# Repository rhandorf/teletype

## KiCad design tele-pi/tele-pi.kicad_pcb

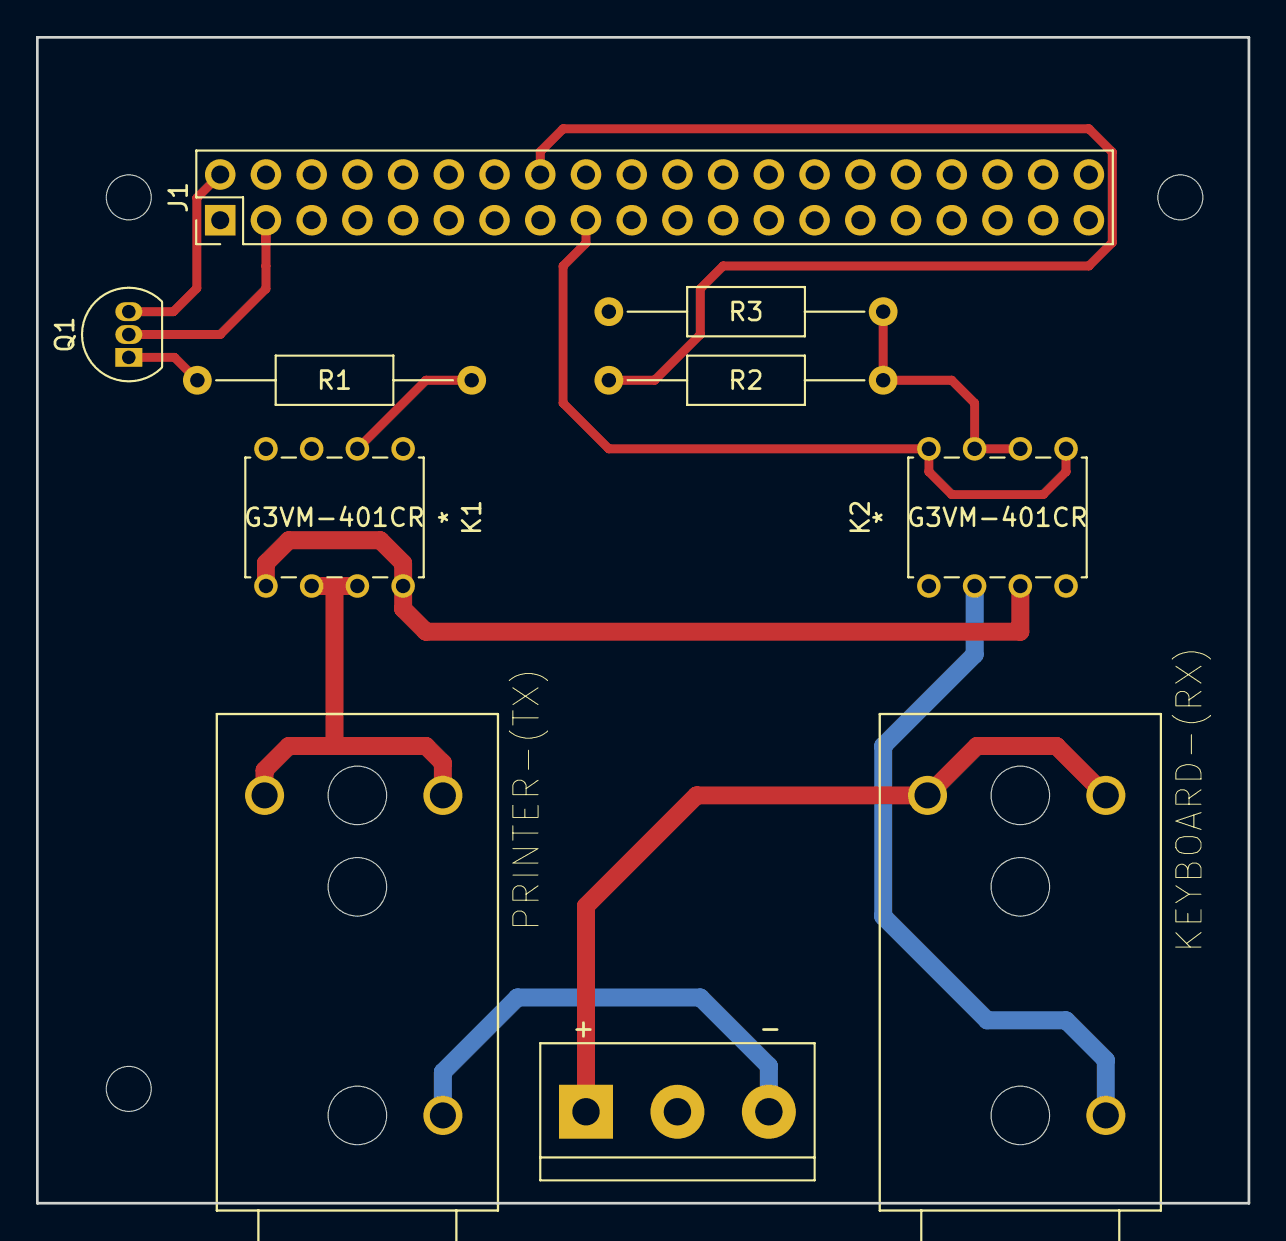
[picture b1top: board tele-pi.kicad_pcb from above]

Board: 2 copper layers, 67.3 x 64.8 mm, 10 parts (0 on the bottom side), 13 nets.

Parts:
+            -: 120VDC; TerminalBlock_bornier-3_P5.08mm
J1: Raspberry_Pi_2_3; PinHeader_2x20_P2.54mm_Vertical
K1, K2: G3VM-401CR
KEYBOARD-(RX): SN37A12A; SWITCHCRAFT_SN37A12A
PRINTER-(TX): SN37A12A; SWITCHCRAFT_SN37A12A
Q1: 2N3904; TO-92_Inline
R1, R2: 3.3k; R_Axial_DIN0207_L6.3mm_D2.5mm_P15.24mm_Horizontal
R3: 100; R_Axial_DIN0207_L6.3mm_D2.5mm_P15.24mm_Horizontal

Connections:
GND: J1.6, J1.9, J1.14, J1.20, J1.25, J1.30, J1.34, J1.39, K1.3, R3.1
unnamed: J1.2, Q1.3
unnamed: J1.3, Q1.2
unnamed: J1.16, R2.1
unnamed: J1.17, K2.5, K2.8
unnamed: + -.3, PRINTER-(TX).S
unnamed: K1.6, K1.7, PRINTER-(TX).T, PRINTER-(TX).TB
unnamed: K2.2, KEYBOARD-(RX).S
unnamed: + -.1, KEYBOARD-(RX).T, KEYBOARD-(RX).TB
unnamed: K1.2, R1.1
unnamed: K1.5, K1.8, K2.3
unnamed: K2.6, K2.7, R2.2, R3.2
unnamed: Q1.1, R1.2

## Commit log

2021-10-04 oopsie dumb file

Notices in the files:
parts and their libraries:
Copyright 2021 Accelerated Designs. All rights reserved.
